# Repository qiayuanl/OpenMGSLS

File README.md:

# OpenMGSLS
**This project was developed in high school, is very naive and low reference value, please refer to it with caution!**

A brief Introduction and demo video show in [my webstie](https://qiayuanliao.netlify.app/project/sls/) 

## Introduction
There have many 3D printing technologies, many of them use the laser to process materials like SLS(Selective Laser Sintering). Move the laser quickly and accurately became an important thing in the 3D printing. Laser galvanometer which widely used in industrial marking has the many advan- tages such as high-speed and high-precision.So this project tries to develop a system which can use laser galvanometer in 3D printing.
## methord
Laser galvanometer works the same as the voltmeter, the volt determines the angle of mirrors which reflect the laser. We use serial to communicate with the computer and receive the GCode(GCode is most widely used nu- merical control programming language), process the GCode and plan, cal- culate the mirrors angle for each movement, use SPI to send the volt data to the DAC module, output the volt and make galvanometer turn to the corresponding angle.Then this poject develop a desktop SLS 3D printer to test the control system.
## date
The galvanometer control system and 3D printer developed in this project are compatible with most 3D printing slicing software(like simplify3D Cura), the laser point movement speed can reach 2,000mm/s, the print accuracy can reach 0.01mm and it can print many complex structures without sup- ports.
## summary
This project develops a system which can use the GCode to control the galvanometer and build a desktop SLS 3D printer base on this system. Rely on this system the printer can do 3D printing faster and more accurately than most of another desktop 3D printer.

## 引言
现存的 3D 打印技术中许多使用激光来加工材料，快速且精确地移动激光非常重要。激光振镜广泛应用于工业打标，具有高速、高精度的优点。本项 目是开发了一套可以在选择性激光烧结 3D 打印机上使用激光振镜的系统。

## 方法
激光振镜的工作原理与电压表相同，电压决定偏转激光的反射镜的角度。 这个项目使用串又与计算机通讯并接收 G代码(G 代码是使用最广泛的数 控编程语言)，对其进行处理规划，计算每个运动对应的电压，使用SPI将数据输出到DAC模块，输出电压，使振镜转到相应的角度。后另外开发了一台选择性激光烧结3D打印机来实验开发的控制系统。

## 数据
这个项目开发的振镜控制系统及3D打印机可以兼容大多数3D打印切片软件如:Simplify3D、Cura。激光点移动速度可以达到 2,000mm/s，打印精度可以达到0.01mm。

## 总结
这个项目开发了一个可以使用 GCode 来控制振镜的系统, 并在此基础上开发了一台桌面级选择性激光烧结3D打印机，可以比其他大多数桌面3D打印机更快，更准确地进行 3D 打印。

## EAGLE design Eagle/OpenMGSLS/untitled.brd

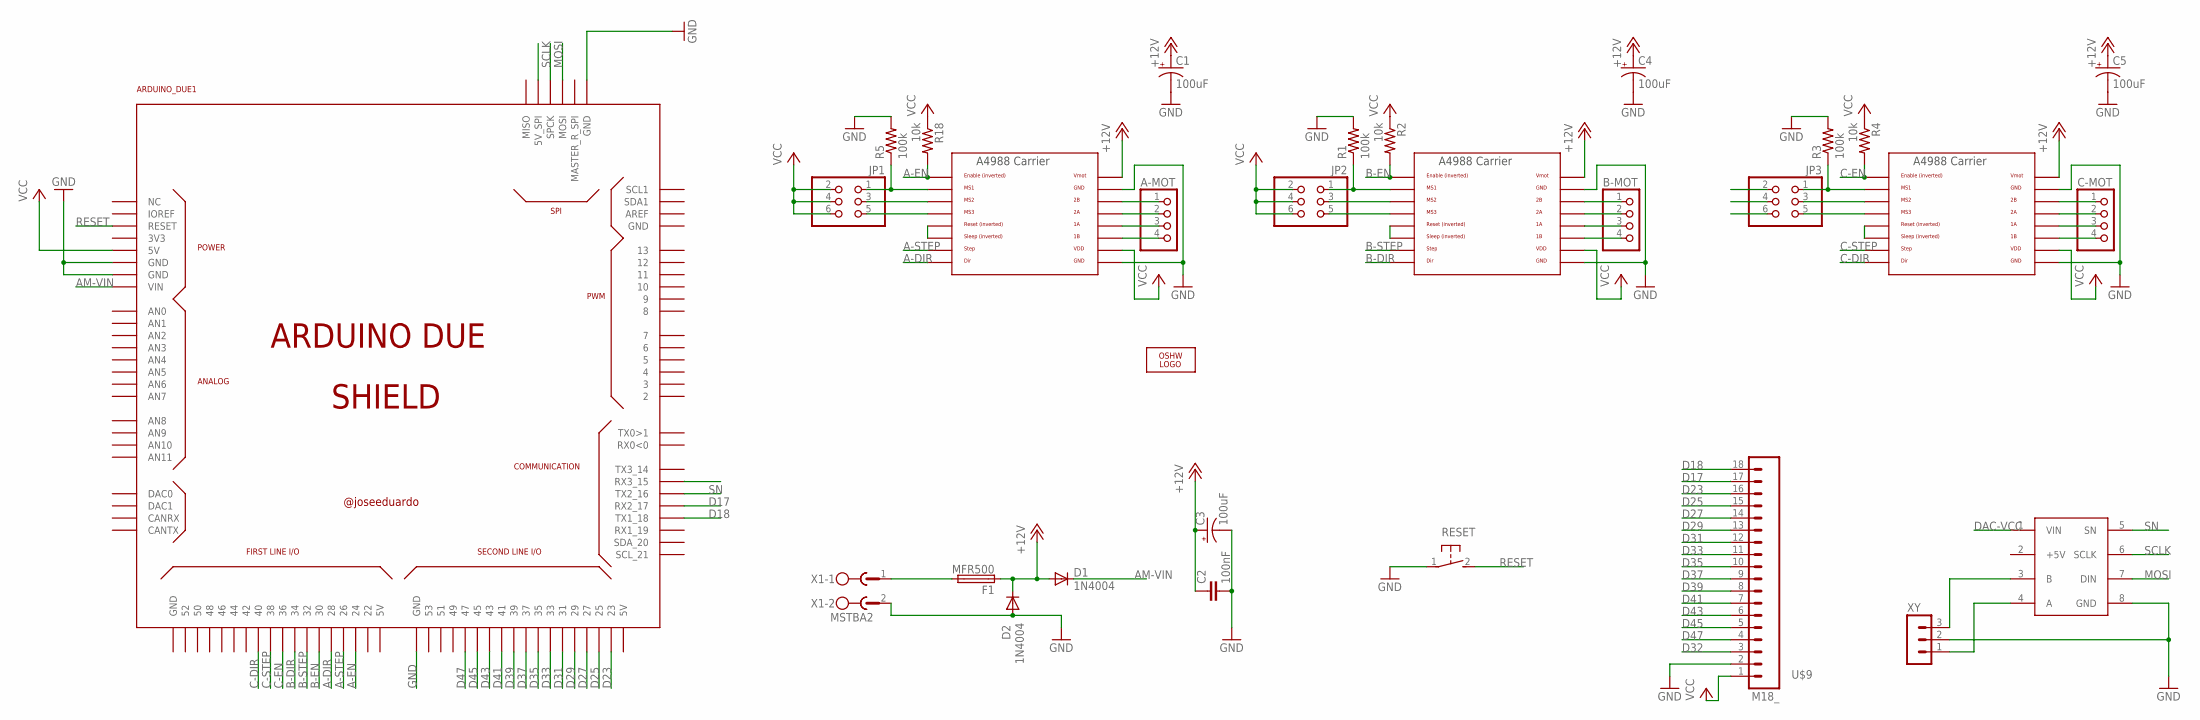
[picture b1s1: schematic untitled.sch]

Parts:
A-MOT: PINHD-1X4; 1X04
ARDUINO_DUE1: ARDUINO_DUE_SHIELD
B-MOT: PINHD-1X4; 1X04
C1, C3, C4, C5: 100uF; 153CLV-0605
C2: 100nF; C0805
C-MOT: PINHD-1X4; 1X04
D1, D2: 1N4004; DO41-10
F1: MFR500
JP1, JP2, JP3: PINHD-2X3; 2X03
LOGO1: OSHW_LOGO_6MILX0200-NT; OSHW_6X200_NOTEXT
R1, R3, R5: 100k; R0805
R2, R4, R18: 10k; R0805
RESET: 31-XX; B3F-31XX
U$1, U$3, U$6: A4988BREAKOUT
U$2: DAC8552
U$9: M18_; 1X18
X1: MSTBA2
XY: 3PIN-HEADER

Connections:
+12V: C1.+, C2.1, C3.+, C4.+, C5.+, D1.A, D2.C, F1.1, U$1.VMOT, U$3.VMOT, U$6.VMOT
A-DIR: ARDUINO_DUE1.28, U$6.DIR
A-EN: ARDUINO_DUE1.24, R18.2, U$6.EN
A-STEP: ARDUINO_DUE1.26, U$6.STEP
AM-VIN: ARDUINO_DUE1.VIN, D1.C
B-DIR: ARDUINO_DUE1.34, U$1.DIR
B-EN: ARDUINO_DUE1.30, R2.2, U$1.EN
B-STEP: ARDUINO_DUE1.32, U$1.STEP
C-DIR: ARDUINO_DUE1.40, U$3.DIR
C-EN: ARDUINO_DUE1.36, R4.2, U$3.EN
C-STEP: ARDUINO_DUE1.38, U$3.STEP
D17: ARDUINO_DUE1.17 (RX2_17), U$9.17
D18: ARDUINO_DUE1.18 (TX1_18), U$9.18
D23: ARDUINO_DUE1.23, U$9.16
D25: ARDUINO_DUE1.25, U$9.15
D27: ARDUINO_DUE1.27, U$9.14
D29: ARDUINO_DUE1.29, U$9.13
D31: ARDUINO_DUE1.31, U$9.12
D32: U$9.3
D33: ARDUINO_DUE1.33, U$9.11
D35: ARDUINO_DUE1.35, U$9.10
D37: ARDUINO_DUE1.37, U$9.9
D39: ARDUINO_DUE1.39, U$9.8
D41: ARDUINO_DUE1.41, U$9.7
D43: ARDUINO_DUE1.43, U$9.6
D45: ARDUINO_DUE1.45, U$9.5
D47: ARDUINO_DUE1.47, U$9.4
DAC-VCC: ARDUINO_DUE1.5V_2 (5V_SPI), U$2.1 (VIN)
GND: ARDUINO_DUE1.GND, ARDUINO_DUE1.GND_1 (GND), ARDUINO_DUE1.GND_3 (GND), ARDUINO_DUE1.GND_5 (GND), C1.-, C2.2, C3.-, C4.-, C5.-, D2.A, R1.2, R3.2, R5.2, RESET.1, U$1.GND, U$1.GND@0 (GND), U$2.8 (GND), U$3.GND, U$3.GND@0 (GND), U$6.GND, U$6.GND@0 (GND), U$9.2, X1.2, XY.2
MOSI: ARDUINO_DUE1.MOSI, U$2.7 (DIN)
unnamed: U$6.RST, U$6.SLP (SLEEP)
unnamed: F1.2, X1.1
unnamed: JP2.5, U$1.MS3
unnamed: JP2.1, R1.1, U$1.MS1
unnamed: JP2.3, U$1.MS2
unnamed: B-MOT.1, U$1.2B
unnamed: B-MOT.2, U$1.2A
unnamed: B-MOT.3, U$1.1A
unnamed: B-MOT.4, U$1.1B
unnamed: U$1.RST, U$1.SLP (SLEEP)
unnamed: JP3.5, U$3.MS3
unnamed: U$2.3 (B), XY.3
unnamed: U$2.4 (A), XY.1
unnamed: JP1.1, R5.1, U$6.MS1
unnamed: JP1.3, U$6.MS2
unnamed: JP3.1, R3.1, U$3.MS1
unnamed: JP3.3, U$3.MS2
unnamed: C-MOT.1, U$3.2B
unnamed: JP1.5, U$6.MS3
unnamed: C-MOT.2, U$3.2A
unnamed: A-MOT.1, U$6.2B
unnamed: A-MOT.2, U$6.2A
unnamed: C-MOT.3, U$3.1A
unnamed: C-MOT.4, U$3.1B
unnamed: U$3.RST, U$3.SLP (SLEEP)
unnamed: A-MOT.3, U$6.1A
unnamed: A-MOT.4, U$6.1B
RESET: ARDUINO_DUE1.RESET, RESET.2 (S)
SCLK: ARDUINO_DUE1.SPCK, U$2.6 (SCLK)
SN: ARDUINO_DUE1.16 (TX2_16), U$2.5 (SN)
VCC: ARDUINO_DUE1.5V0 (5V), JP1.2, JP1.4, JP1.6, JP2.2, JP2.4, JP2.6, JP3.2, JP3.4, JP3.6, R2.1, R4.1, R18.1, U$1.VDD, U$3.VDD, U$6.VDD, U$9.1
Z-MIN: ARDUINO_DUE1.15 (RX3_15)

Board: 2 copper layers, 30 parts (0 on the bottom side), 60 nets, no tracks yet.

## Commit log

2017-12-13 add a unfinshed Chinese papaer use Latex
2017-12-13 delete
2017-12-17 add more about the paper
2017-12-20 finish paper
2018-03-23 add docs
2018-03-23 Please enter the commit message for your changes. Lines starting
2018-08-05 add eagle file
2018-08-05 add cad drawing file
2018-08-05 add arduino code
2018-08-05 add more infor about README
2018-08-05 rewrite README.md
